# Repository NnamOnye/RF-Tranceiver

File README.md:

# RF-Transceiver on 2.4GHz
# i utilized Interference Management, when developing the microstrip.
# i also utilized impedance matching,and ground zones for noise reduction.
# This design can be used as a receiver and transmitter depending on your application.
# The B.O.M in Production has the components i used.
# Designed Using Kicad ECAD
# KiCAD Download --> https://www.kicad.org/download/

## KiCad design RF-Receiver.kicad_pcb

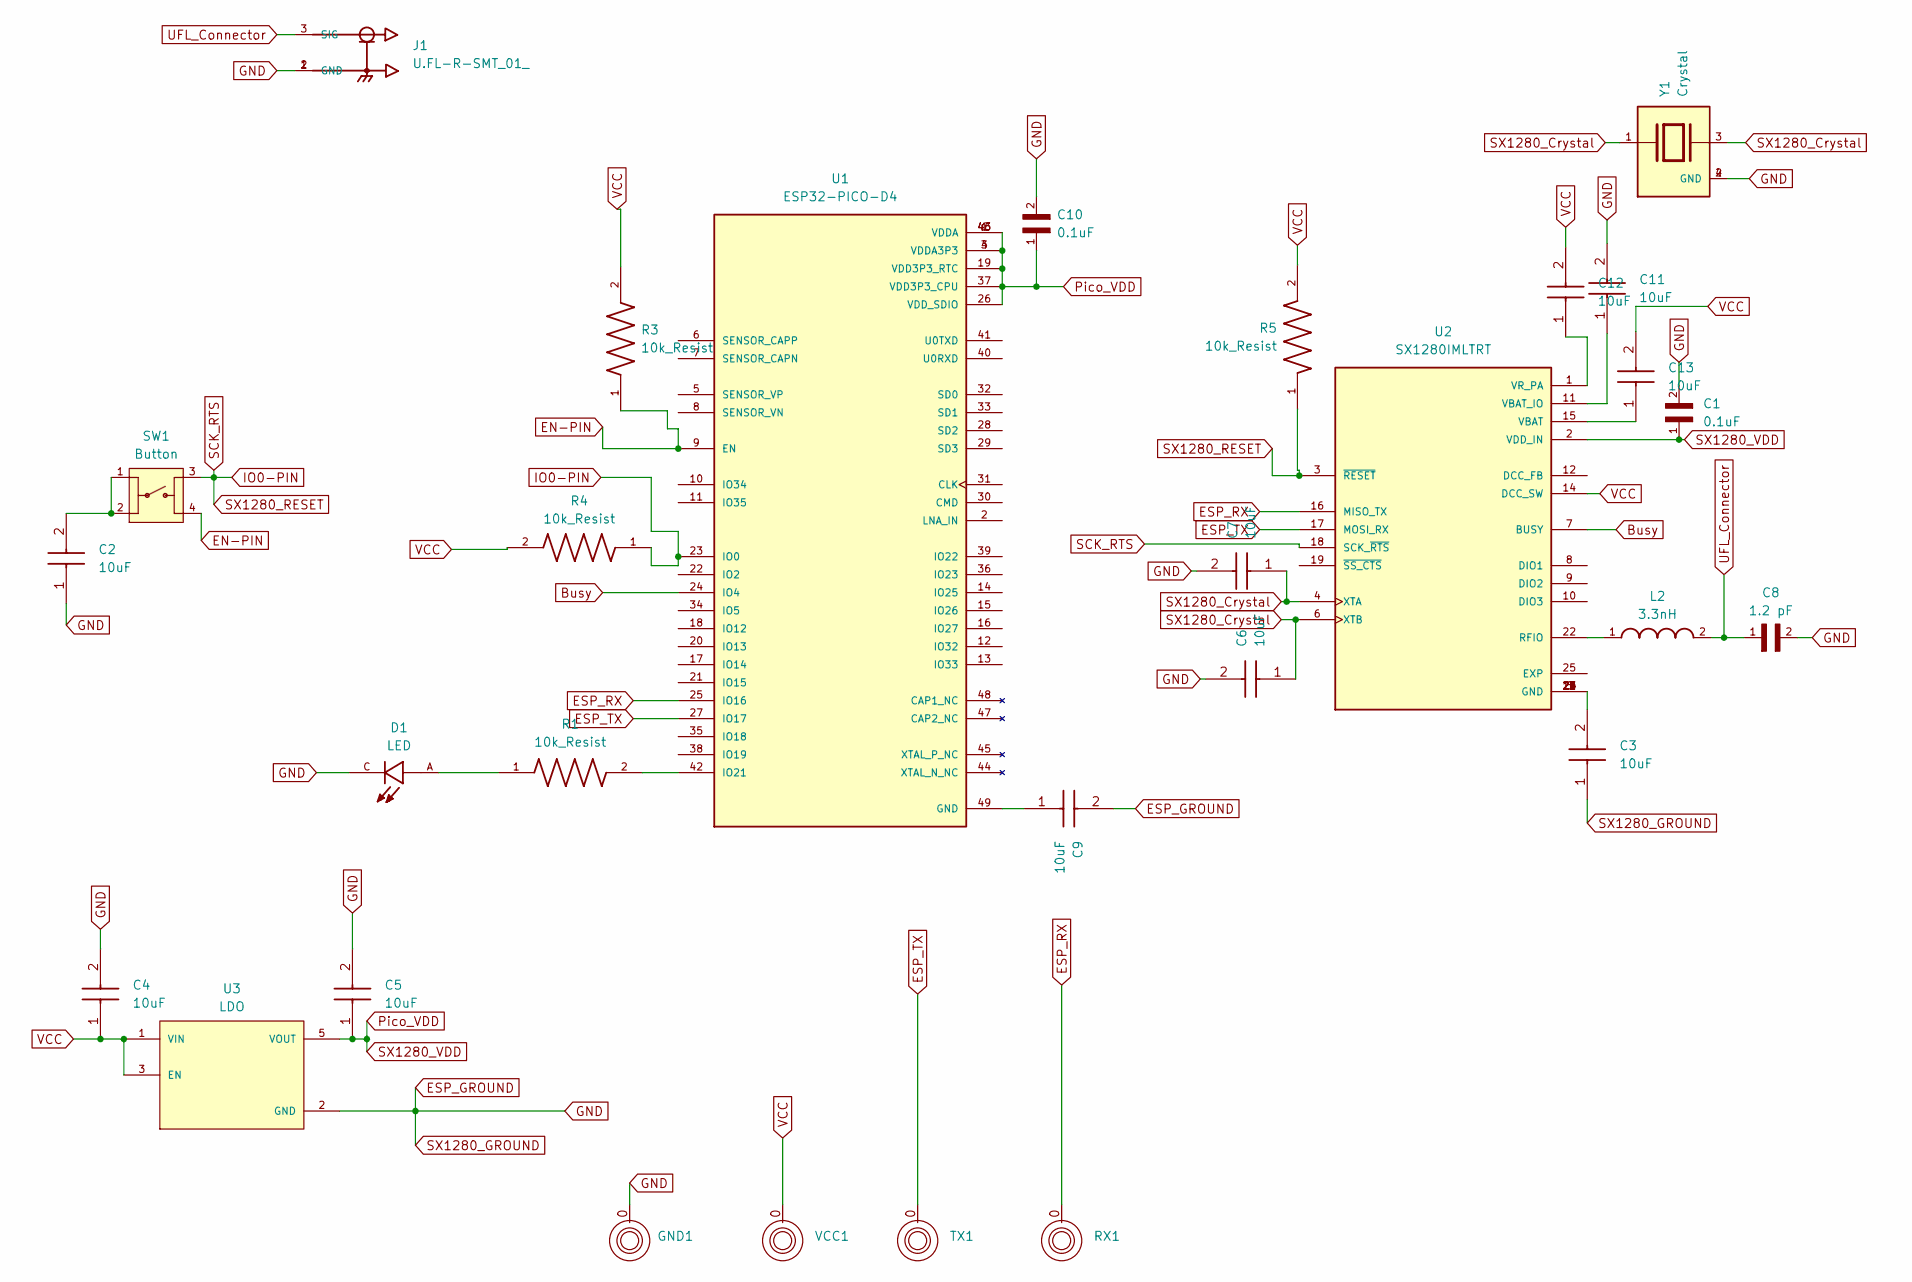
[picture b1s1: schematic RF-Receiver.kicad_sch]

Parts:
C1, C10: 0.1uF; Decoup_Capacitor_0_1uF
C2, C3, C4, C5, C6, C7, C9, C11, C12, C13: 10uF; Capacitor10uF; Manufacturer_Part_Number C1608X7R1A106M080AT; Mouser Part Number 810-C1608X7R1A106M08
C8: 1.2 pF; Capacitor_1_2pF
D1: LED; LED_SML_D12M1WT86; PARTREV 007
GND1: Via_Pad
J1: U.FL-R-SMT_01_; U.FL_R_SMT_01
L2: 3.3nH; Inductor_3_3nH
R1, R3, R4, R5: 10k_Resist; 10kResist; PARTREV 3/1/2020
RX1: Via_Pad
SW1: Button; boot_button1; PARTREV V
TX1: Via_Pad
U1: ESP32-PICO-D4; ESP32_PICO_D4; PARTREV v1.9
U2: SX1280IMLTRT; PARTREV 3.3
U3: LDO; LDO_3v_500mA; PARTREV B
VCC1: Via_Pad
Y1: Crystal; Crysta_RF_40MHz; PARTREV N/A

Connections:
Busy: U1.24 (IO4), U2.7 (BUSY)
EN-PIN: R3.1, SW1.4, U1.9 (EN)
ESP_GROUND: C1.2, C2.1, C3.1, C4.2, C5.2, C6.2, C7.2, C8.2, C9.2, C10.2, C11.2, D1.C, GND1.0, J1.1 (GND), J1.2 (GND), U3.2 (GND), Y1.2 (GND), Y1.4 (GND)
ESP_RX: RX1.0, U1.25 (IO16), U2.16 (MISO_TX)
ESP_TX: TX1.0, U1.27 (IO17), U2.17 (MOSI_RX)
IO0-PIN: R4.1, R5.1, SW1.3, U1.23 (IO0), U2.3 (~RESET), U2.18 (SCK_~RTS)
unnamed: C2.2, SW1.1, SW1.2
unnamed: C3.2, U2.5 (GND), U2.13 (GND), U2.20 (GND), U2.21 (GND), U2.23 (GND), U2.24 (GND)
unnamed: D1.A, R1.1
unnamed: C9.1, U1.49 (GND)
unnamed: R1.2, U1.42 (IO21)
unnamed: L2.1, U2.22 (RFIO)
unnamed: C13.1, U2.15 (VBAT)
unnamed: C11.1, U2.11 (VBAT_IO)
unnamed: C12.1, U2.1 (VR_PA)
Pico_VDD: C1.1, C5.1, C10.1, U1.1 (VDDA), U1.3 (VDDA3P3), U1.4 (VDDA3P3), U1.19 (VDD3P3_RTC), U1.26 (VDD_SDIO), U1.37 (VDD3P3_CPU), U1.43 (VDDA), U1.46 (VDDA), U2.2 (VDD_IN), U3.5 (VOUT)
SX1280_Crystal: C6.1, C7.1, U2.4 (XTA), U2.6 (XTB), Y1.1, Y1.3
UFL_Connector: C8.1, J1.3 (SIG), L2.2
VCC: C4.1, C12.2, C13.2, R3.2, R4.2, R5.2, U2.14 (DCC_SW), U3.1 (VIN), U3.3 (EN), VCC1.0

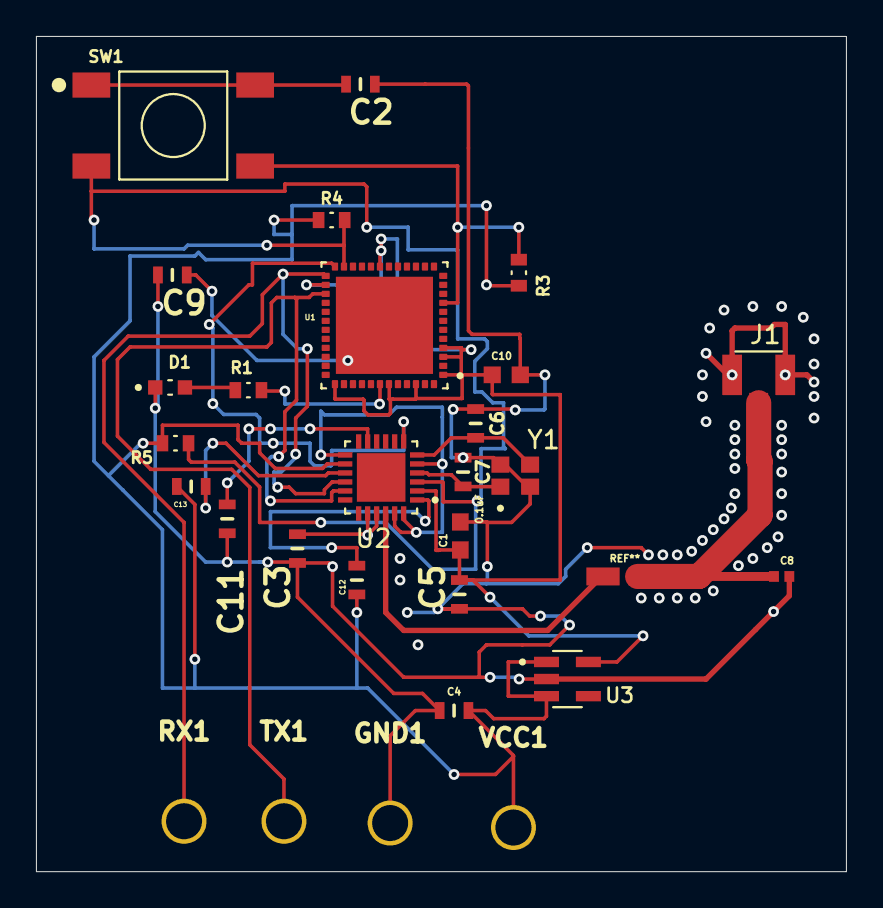
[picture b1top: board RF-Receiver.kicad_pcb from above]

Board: 2 copper layers, 45.0 x 46.4 mm, 28 parts (0 on the bottom side), 18 nets.

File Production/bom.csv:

Designator,Footprint,Quantity,Value,LCSC Part #
"C1, C10",Decoup_Capacitor_0_1uF,2,0.1uF,
"C2, C3, C4, C5, C6, C7, C9",Capacitor10uF,7,10uF,
C8,Capacitor_1_2pF,1,1.2 pF,
D1,LED_SML_D12M1WT86,1,LED,
"GND1, RX1, TX1, VCC1",Via_Pad,4,~,
J1,U.FL_R_SMT_01,1,U.FL-R-SMT_01_,
"R1,R3",10kResist,2,10k_Resist,
R2,1kResist,1,1KOhms,
SW1,boot_button1,1,Button,
U1,ESP32_PICO_D4,1,ESP32-PICO-D4,
U2,SX1280IMLTRT,1,SX1280IMLTRT,
U3,LDO_3v_500mA,1,LDO,
Y1,Crysta_RF_40MHz,1,Crystal,
L2,LQW15AN3N3G8ZD,1,Inductor_3.3nH,

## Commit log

2025-07-18 README.md
2025-07-18 Production
2025-07-31 Schematic Screenshot
2025-07-31 RF-Receiver-Board.jpeg
2025-07-31 RF-Receiver-Schematic.jpg
2025-08-04 bom.csv
2025-08-12 RF-Receiver Board
2025-08-12 Production zip for ordering
2025-08-12 RF-Transceiver
2025-08-12 Other Project Files
2025-09-08 Project files
    Problem: EN Pin floating causing "no power" issue
    Fix: Tied EN Pin to 10KOhm Resistor and VDD
2025-09-08 Updated TransceiverV3
2025-09-08 ToolKit
2025-09-08 Project Files
    Update to board and schematic
2025-09-08 project files
2025-09-09 Updated Design Addressing No Power Up
    Updated Design Addressing no power up during uart to usb flashing
2025-09-09 REUPLOAD
